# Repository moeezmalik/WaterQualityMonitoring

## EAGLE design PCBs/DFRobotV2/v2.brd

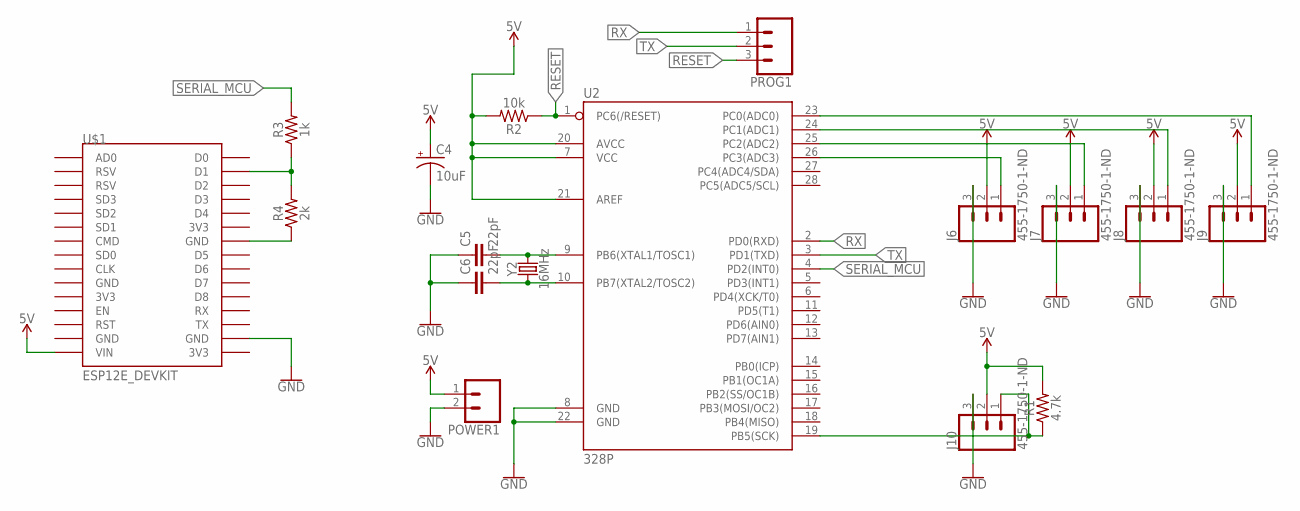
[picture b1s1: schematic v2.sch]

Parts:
C4: 10uF; CPOL-RADIAL-2.5MM-5MM
C5, C6: 22pF; CAP-PTH-2.54
J6, J7, J8, J9, J10: 455-1750-1-ND; 1X03
POWER1: CONN_02; 1X02
PROG1: CONN_03; 1X03
R1: 4.7k; AXIAL-0.3
R2: 10k; AXIAL-0.3
R3: 1k; AXIAL-0.3
R4: 2k; AXIAL-0.3
U2: 328P; DIP28
U$1: ESP12E_DEVKIT
Y2: 16MHz; HC49US

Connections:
5V: C4.1 (+), J6.2, J7.2, J8.2, J9.2, J10.2, POWER1.1, R1.P$2 (2), R2.P$2 (2), U2.7 (VCC), U2.20 (AVCC), U2.21 (AREF), U$1.VIN
GND: C4.2 (-), C5.1, C6.1, J6.3, J7.3, J8.3, J9.3, J10.3, POWER1.2, U2.8 (GND), U2.22 (GND), U$1.GND@3 (GND)
unnamed: C5.2, U2.9 (PB6(XTAL1/TOSC1)), Y2.2
unnamed: C6.2, U2.10 (PB7(XTAL2/TOSC2)), Y2.1
unnamed: J6.1, U2.26 (PC3(ADC3))
unnamed: J7.1, U2.25 (PC2(ADC2))
unnamed: J8.1, U2.24 (PC1(ADC1))
unnamed: J9.1, U2.23 (PC0(ADC0))
unnamed: R3.P$1 (1), R4.P$2 (2), U$1.D1
unnamed: J10.1, R1.P$1 (1), U2.19 (PB5(SCK))
unnamed: R4.P$1 (1), U$1.GND@2 (GND)
RESET: PROG1.3, R2.P$1 (1), U2.1 (PC6(/RESET))
RX: PROG1.1, U2.2 (PD0(RXD))
SERIAL_MCU: R3.P$2 (2), U2.4 (PD2(INT0))
TX: PROG1.2, U2.3 (PD1(TXD))

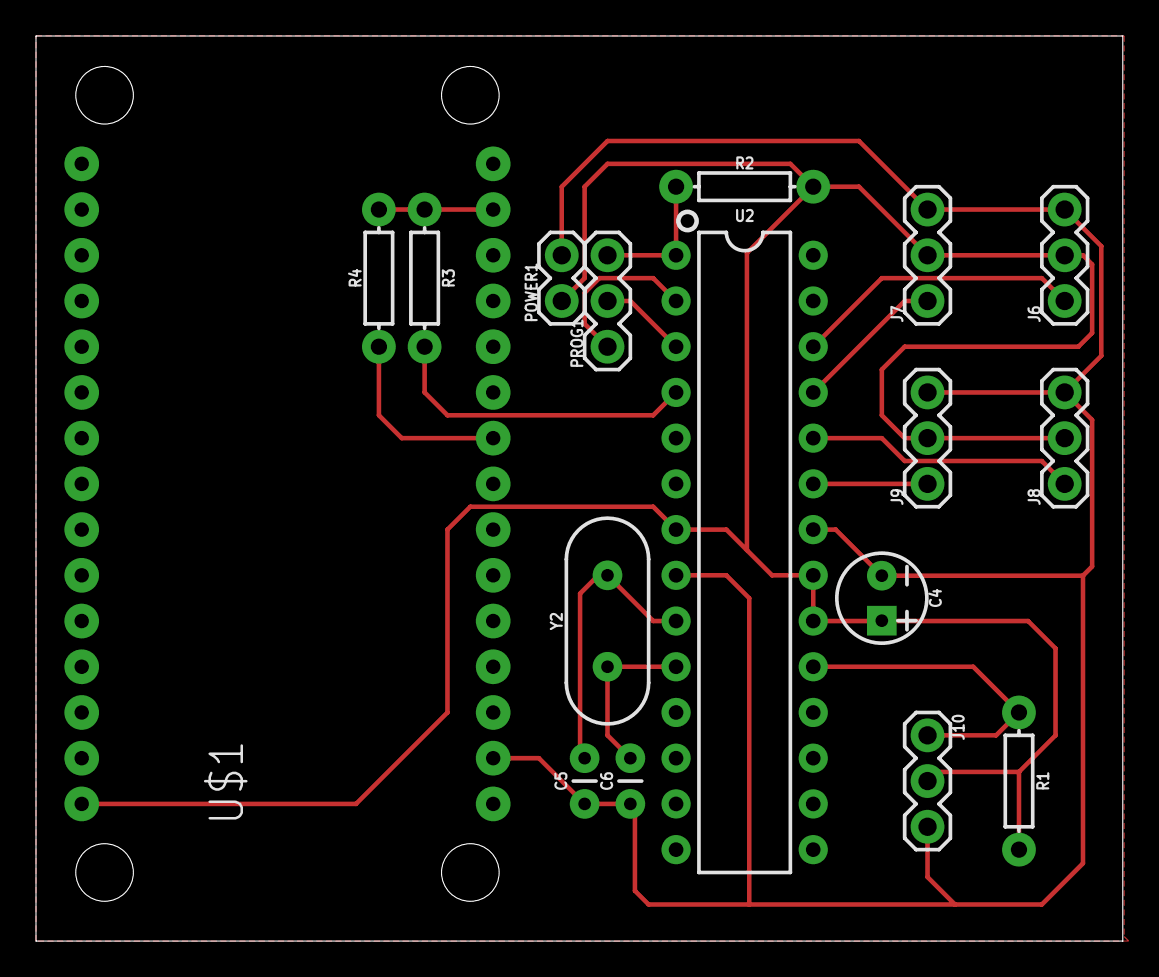
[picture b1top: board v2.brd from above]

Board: 2 copper layers, 60.4 x 50.3 mm, 17 parts (0 on the bottom side), 15 nets.

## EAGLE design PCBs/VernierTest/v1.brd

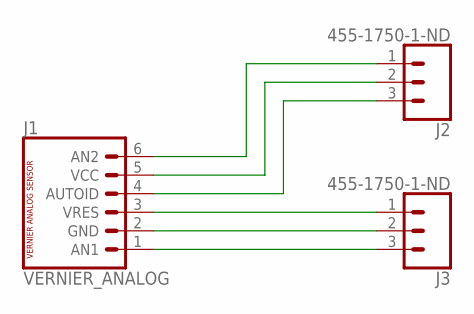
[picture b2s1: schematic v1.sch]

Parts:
J1: VERNIER_ANALOG; BTA
J2, J3: 455-1750-1-ND; 1X03

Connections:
unnamed: J1.1 (AN1), J3.3
unnamed: J1.2 (GND), J3.2
unnamed: J1.3 (VRES), J3.1
unnamed: J1.4 (AUTOID), J2.3
unnamed: J1.5 (VCC), J2.2
unnamed: J1.6 (AN2), J2.1

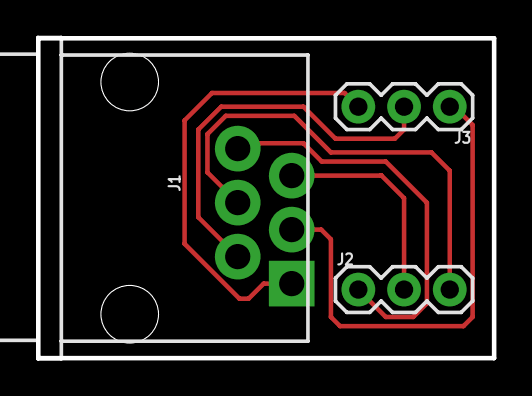
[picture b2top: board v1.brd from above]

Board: 2 copper layers, 25.3 x 17.8 mm, 3 parts (0 on the bottom side), 6 nets.

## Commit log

2020-01-15 Test PCB for the BTA Connector
2020-03-05 Housekeeping
2020-07-03 refreshing

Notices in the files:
parts and their libraries:
SparkFun-Capacitors: Licensing: Creative Commons ShareAlike 4.0 International - https://creativecommons.org/licenses/by-sa/4.0
